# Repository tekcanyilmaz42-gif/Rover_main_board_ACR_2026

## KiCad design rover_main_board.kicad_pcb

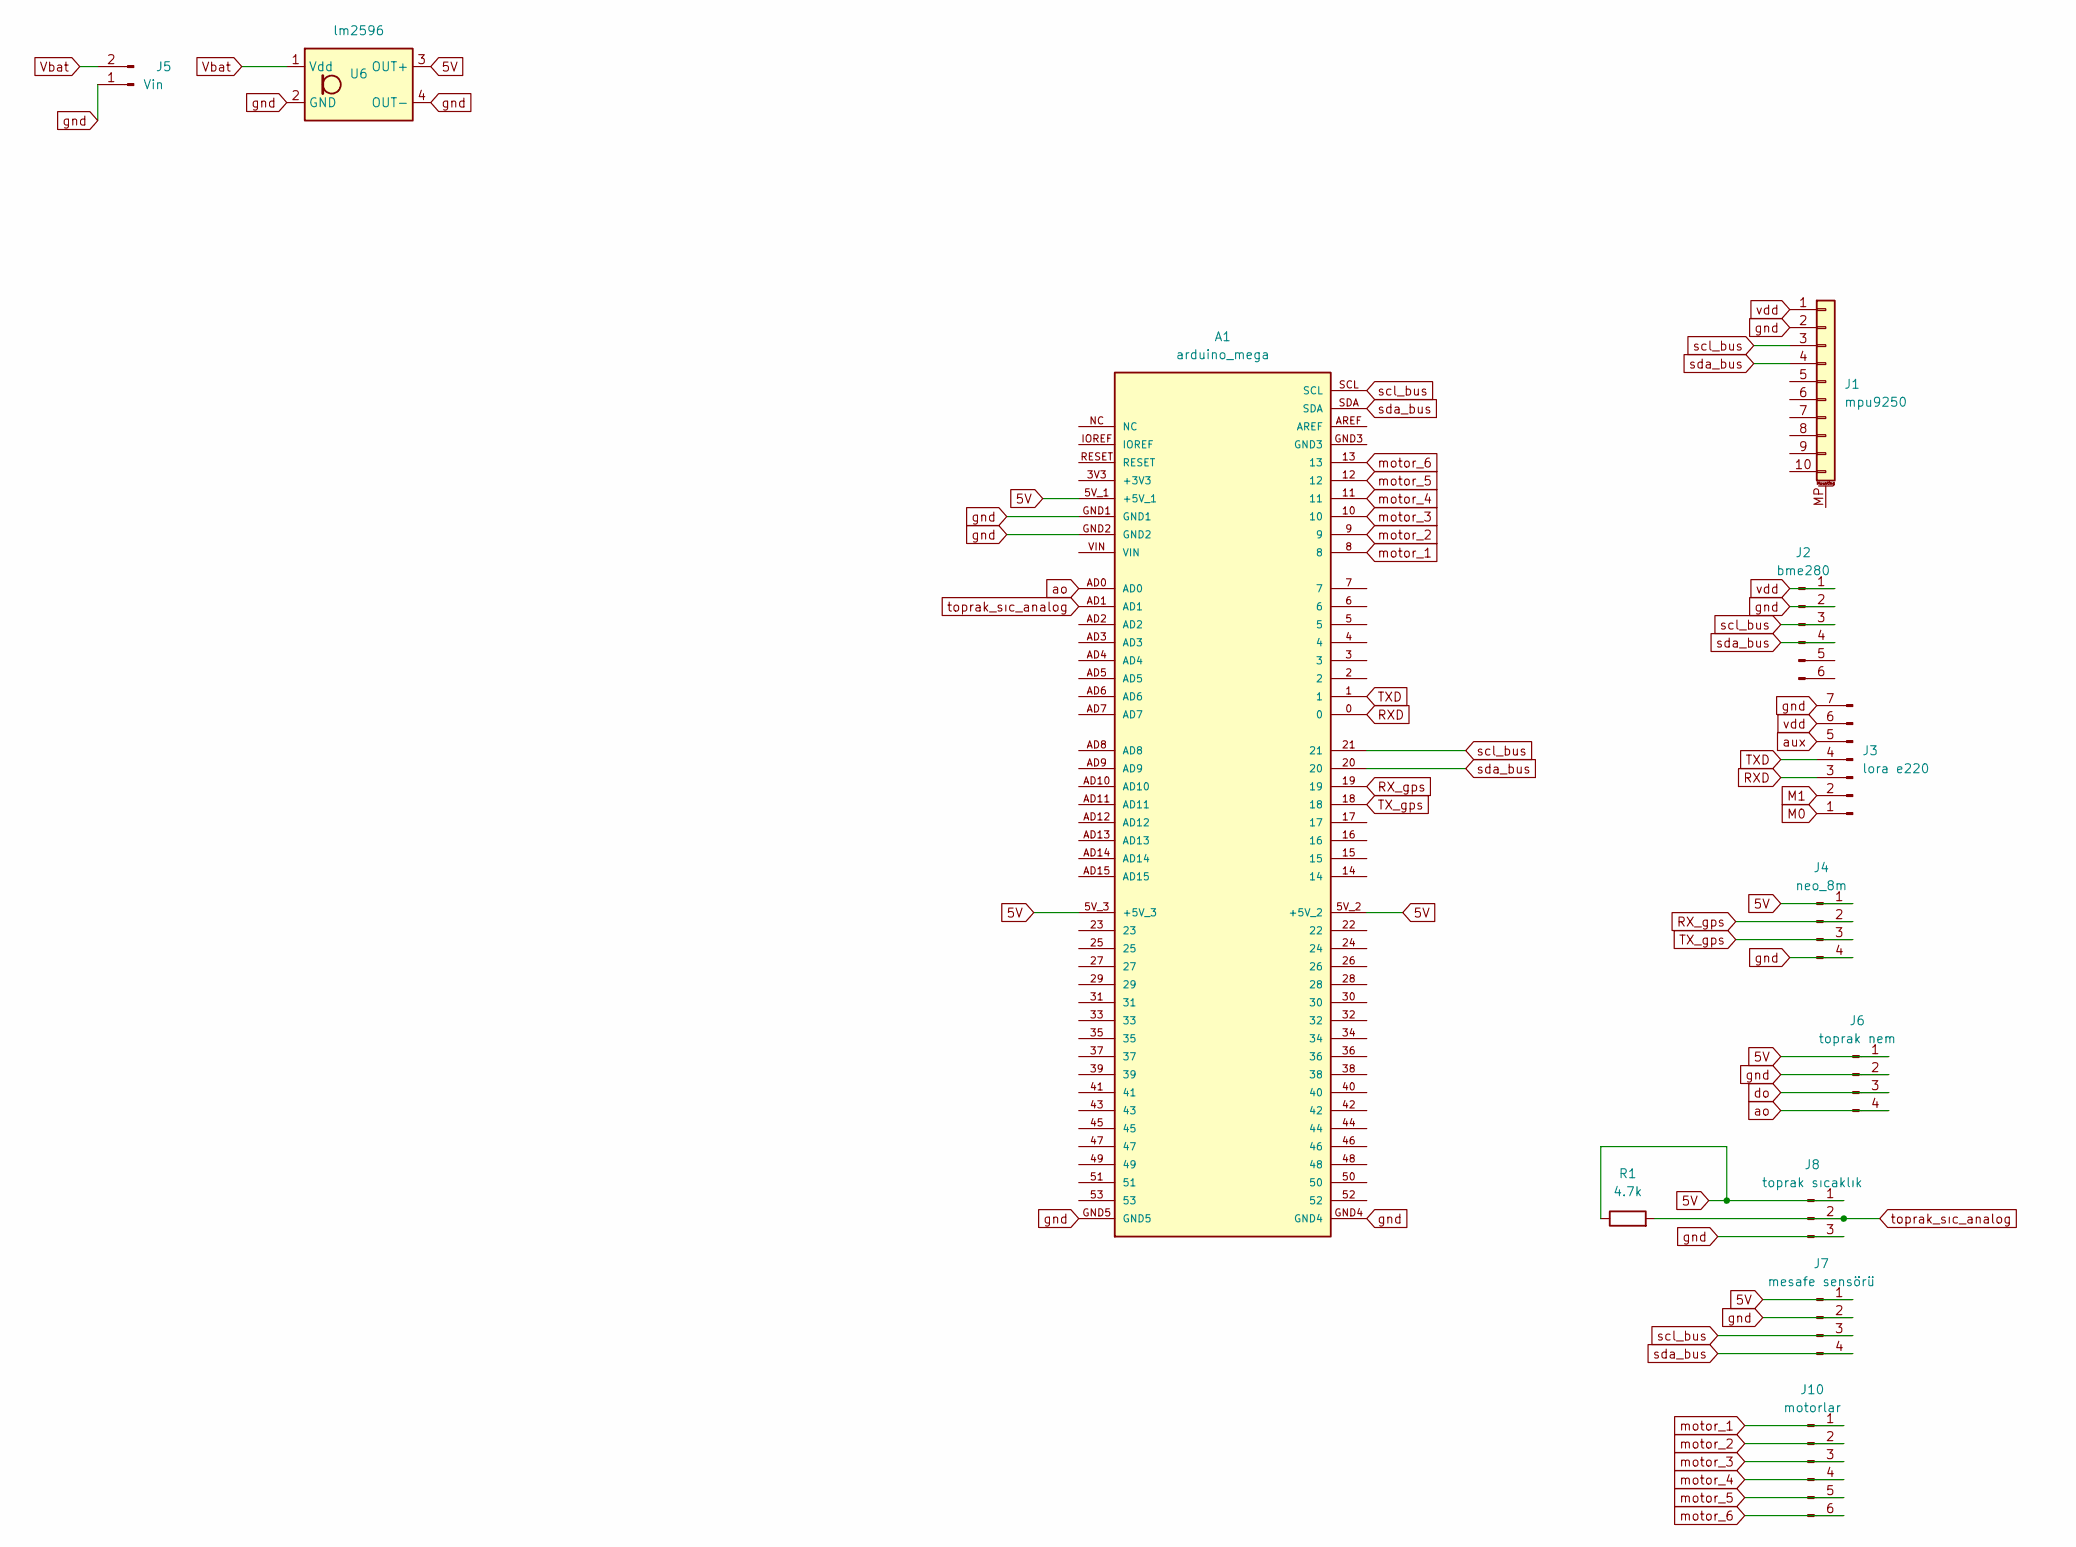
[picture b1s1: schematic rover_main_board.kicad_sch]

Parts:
A1: arduino_mega; PARTREV 3
J1: mpu9250; PinSocket_1x10_P2.54mm_Vertical
J2: bme280; PinSocket_1x06_P2.54mm_Vertical
J3: lora e220; PinSocket_1x07_P2.54mm_Vertical
J4: neo_8m; PinSocket_1x04_P2.54mm_Vertical
J5: Vin; TerminalBlock_Phoenix_MKDS-1,5-2-5.08_1x02_P5.08mm_Horizont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
J6: toprak nem; TerminalBlock_Phoenix_MKDS-1,5-4-5.08_1x04_P5.08mm_Horizont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
J7: mesafe sensörü; TerminalBlock_Phoenix_MKDS-1,5-4-5.08_1x04_P5.08mm_Horizont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
J8: toprak sıcaklık; TerminalBlock_Phoenix_MKDS-1,5-3-5.08_1x03_P5.08mm_Horizont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
J10: motorlar; TerminalBlock_Phoenix_MKDS-1,5-6-5.08_1x06_P5.08mm_Horizont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
R1: 4.7k; R_Axial_DIN0204_L3.6mm_D1.6mm_P1.90mm_Vertical
U6: lm2596; 2596_module

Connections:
M0: J3.1
M1: J3.2
RXD: A1.0, J3.3
RX_gps: A1.19, J4.2
TXD: A1.1, J3.4
TX_gps: A1.18, J4.3
Vbat: J5.2, U6.1 (Vdd)
ao: A1.AD0, J6.4
aux: J3.5
do: J6.3
gnd: A1.GND1, A1.GND2, A1.GND4, A1.GND5, J1.2, J2.2, J3.7, J4.4, J5.1, J6.2, J7.2, J8.3, U6.2 (GND), U6.4 (OUT-)
motor_1: A1.8, J10.1
motor_2: A1.9, J10.2
motor_3: A1.10, J10.3
motor_4: A1.11, J10.4
motor_5: A1.12, J10.5
motor_6: A1.13, J10.6
scl_bus: A1.21, A1.SCL, J1.3, J2.3, J7.3
sda_bus: A1.20, A1.SDA, J1.4, J2.4, J7.4
toprak_sıc_analog: A1.AD1, J8.2, R1.2

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
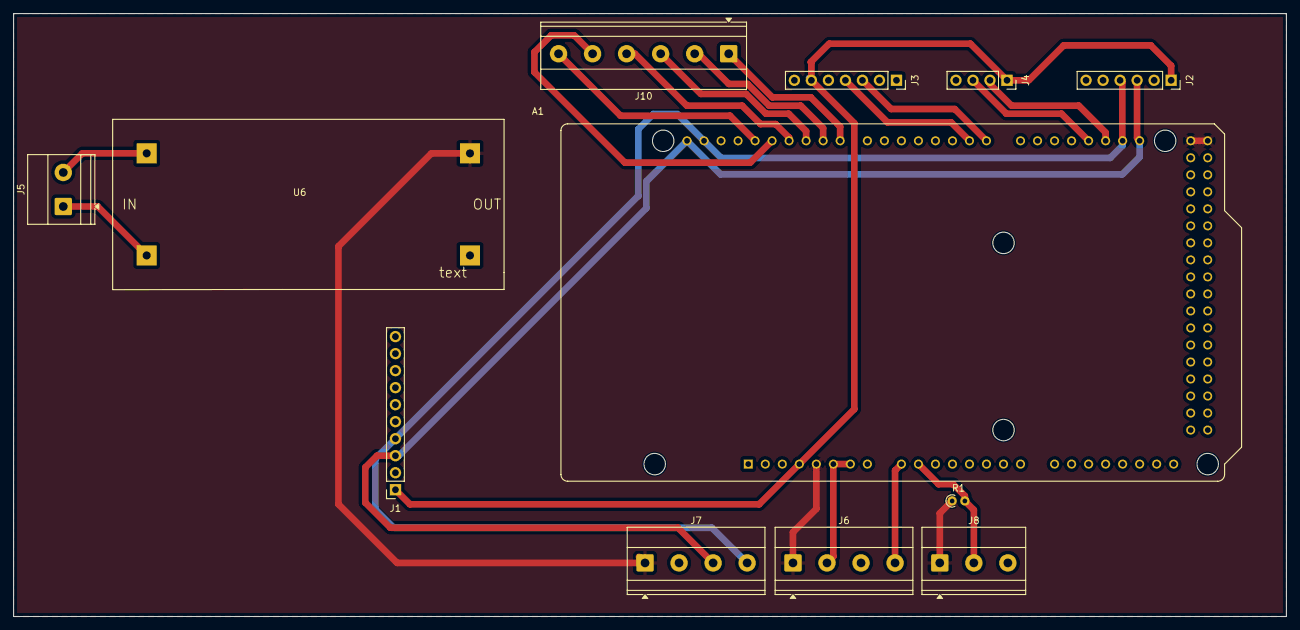
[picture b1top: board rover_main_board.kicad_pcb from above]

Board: 2 copper layers, 190.0 x 90.0 mm, 12 parts (0 on the bottom side), 18 nets.
